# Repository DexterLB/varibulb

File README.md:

An incandescent/halogen light intensity controller that fits in a switch
slot and uses a triac phase cutout for regulating the power

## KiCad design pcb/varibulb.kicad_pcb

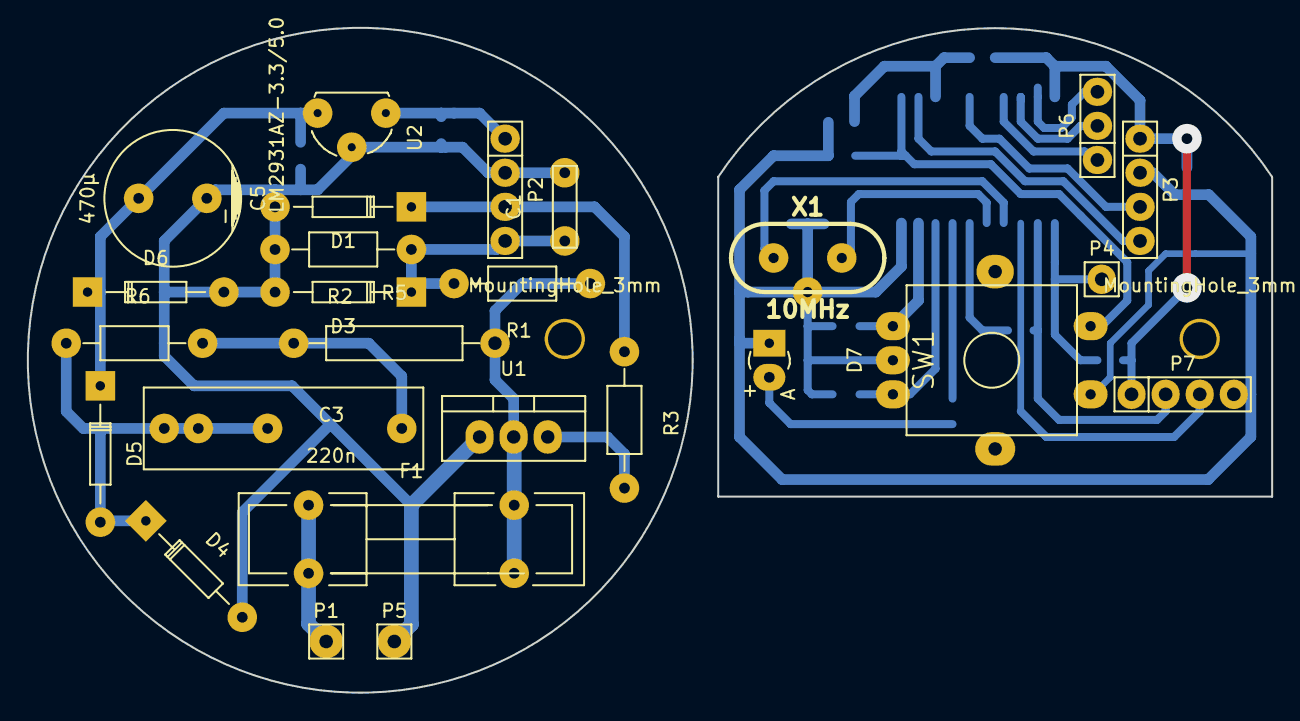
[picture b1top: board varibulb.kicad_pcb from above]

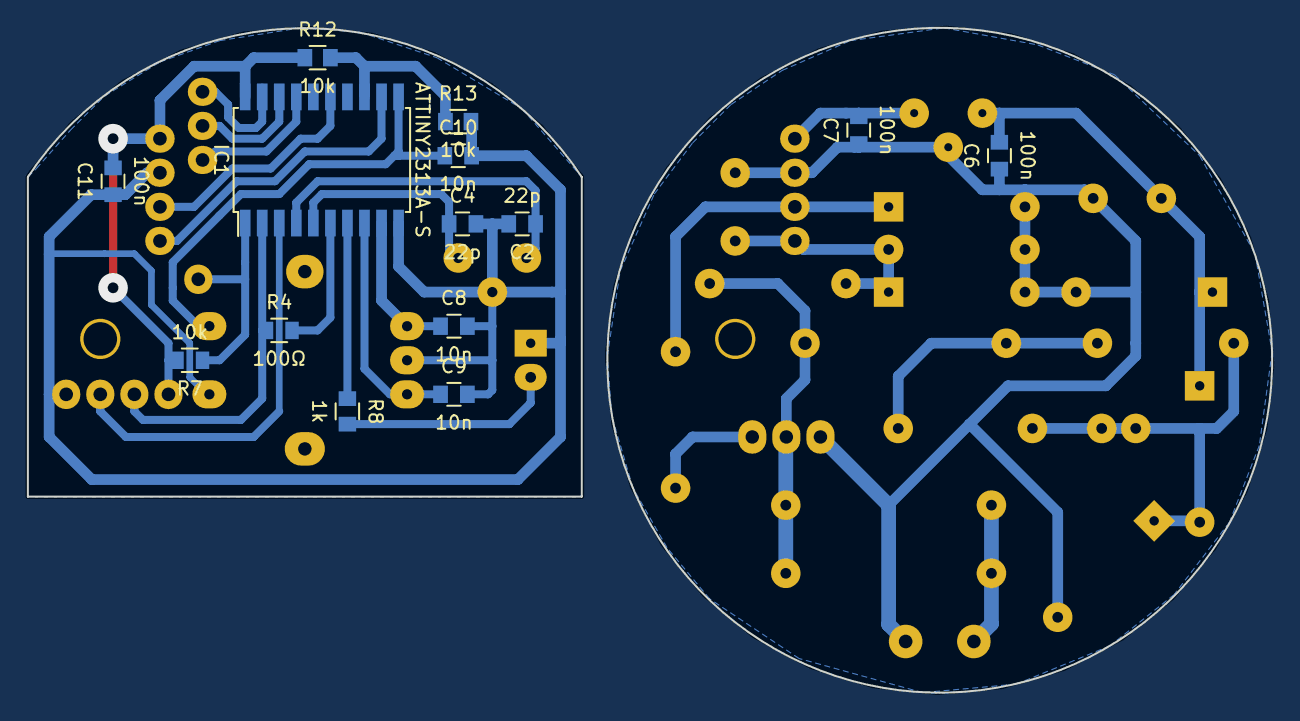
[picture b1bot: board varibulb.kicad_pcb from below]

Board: 2 copper layers, 92.7 x 49.5 mm, 42 parts (14 on the bottom side), 29 nets.

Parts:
C1: 100p; Capacitor6MMDiscRM5
C2, C4: 22p; C_0805
C3: 220n; Capacitor13x6x12mmRM10
C5: 470μ; Capacitor10x16RM5
C6, C7, C11: 100n; C_0805
C8, C9, C10: 10n; C_0805
D1: 5v; Diode_DO-35_SOD27_Horizontal_RM10
D3: 3.3v; Diode_DO-35_SOD27_Horizontal_RM10
D4, D5: DIODE; Diode_DO-35_SOD27_Horizontal_RM10
D6: 8.2v; Diode_DO-35_SOD27_Horizontal_RM10
D7: LED; Diode_LED_3mm_round_vertical
F1: FUSE; Fuseholder5x20_horiz_open_lateral_Type-II
IC1: ATTINY2313A-S; SOIC-20_7.5x12.8mm_Pitch1.27mm
MountingHole_3mm, MountingHole_3mm#2: VAL**; MountingHole_3mm
P1: MAINS LIVE; Pin_Header_Straight_1x01
P2, P3: BOARD; Pin_Header_Straight_1x04
P4: RESET; Pin_Header_Straight_1x01
P5: MAINS GROUND; Pin_Header_Straight_1x01
P6: ISP; Pin_Header_Straight_1x03
P7: COMM; Pin_Header_Straight_1x04
R1: 2.7M; Resistor_Horizontal_RM10mm
R2: 560k; Resistor_Horizontal_RM10mm
R3: 470Ω; Resistor_Horizontal_RM10mm
R4: 100Ω; R_0805
R5: 510Ω; Resistor_Horizontal_RM15mm
R6: 1M; Resistor_Horizontal_RM10mm
R7, R12, R13: 10k; R_0805
R8: 1k; R_0805
SW1: ENCODER
U1: TRIAC; TO-220_Neutral123_Vertical
U2: LM2931AZ-3.3/5.0; TO-92-Free-molded-wide
X1: 10MHz; HC-49V

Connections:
/PHASE: IC1.15, P3.3
/SENSE: IC1.12, P3.4
GND: C2.2, C4.2, C8.2, C9.2, C10.2, C11.1, D7.2, IC1.10, P3.2, P7.4, R13.2, SW1.2, SW1.5, X1.0
GNDREF: C1.2, C5.2, C6.1, C7.1, D1.1, D3.1, D4.1, D6.1, P2.2, P5.1, R2.2, U1.1, U2.2
unnamed: C1.1, D3.2, P2.4, R1.2, R2.1
unnamed: C2.1, IC1.4, X1.1
unnamed: C3.1, D4.2, D5.1, R6.1
unnamed: C3.2, R5.1, R6.2
unnamed: C4.1, IC1.5, X1.2
unnamed: C5.1, C6.2, D5.2, D6.2, U2.3
unnamed: C7.2, P2.1, U2.1
unnamed: C8.1, IC1.9, SW1.1
unnamed: C9.1, IC1.8, SW1.3
unnamed: C10.1, IC1.11, SW1.4
unnamed: D1.2, P2.3, R3.1
unnamed: D7.1, R8.2
unnamed: F1.1, P1.1
unnamed: F1.2, R1.1, R5.2, U1.2
unnamed: IC1.1, P4.1, R7.1
unnamed: IC1.2, P7.2, R4.1
unnamed: IC1.3, P7.3
unnamed: IC1.6, R4.2
unnamed: IC1.7, R8.1
unnamed: IC1.13, R12.2, R13.1
unnamed: IC1.17, P6.1
unnamed: IC1.18, P6.2
unnamed: IC1.19, P6.3
unnamed: R3.2, U1.3
VCC: C11.2, IC1.20, P3.1, P7.1, R7.2, R12.1

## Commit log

2016-02-05 add readme and gitignore
2016-02-05 add avr building code
2016-02-06 start drawing schematic
2016-02-06 finish power supply
2016-02-06 finish overall schematic
2016-02-06 fix wrong line
2016-02-15 remake schematic to use a capacitor for power conversion
2016-02-16 annotate schematic and fix erc errors
2016-02-16 fix some values
2016-02-16 add receiver code
2016-02-20 change frequency
2016-02-20 it works
2016-02-20 basic pulsing works
2016-02-21 use timer's output compare for waveform generation
2016-02-21 use short pulses for triac
2016-02-21 simplify code
2016-02-21 add encoder decoding
2016-02-21 add smooth weakness
2016-02-21 some fixes
2016-02-21 change frequency to 20MHz
2016-02-22 add componente to pcb
2016-02-22 arrange some components
2016-02-22 arrange more components
2016-02-22 two PCBs
2016-02-22 arrange power pcb
2016-02-25 set appropriate track widths
2016-02-25 move capacitor
2016-02-25 this sucks so much..
2016-02-26 arrange some more components
2016-02-28 finish pcb
2016-02-28 add filled zone
2016-02-29 remove the filled zone
2016-02-29 center edge outlines properly
2016-02-29 bigger capacitors
2016-02-29 activate avr internal pullup resistors
2016-02-29 implement (untested) message processing
2016-03-01 update schematic to last changes
2016-03-09 make PCB prints
2016-03-09 flip print
2016-03-09 prettify schematic print
